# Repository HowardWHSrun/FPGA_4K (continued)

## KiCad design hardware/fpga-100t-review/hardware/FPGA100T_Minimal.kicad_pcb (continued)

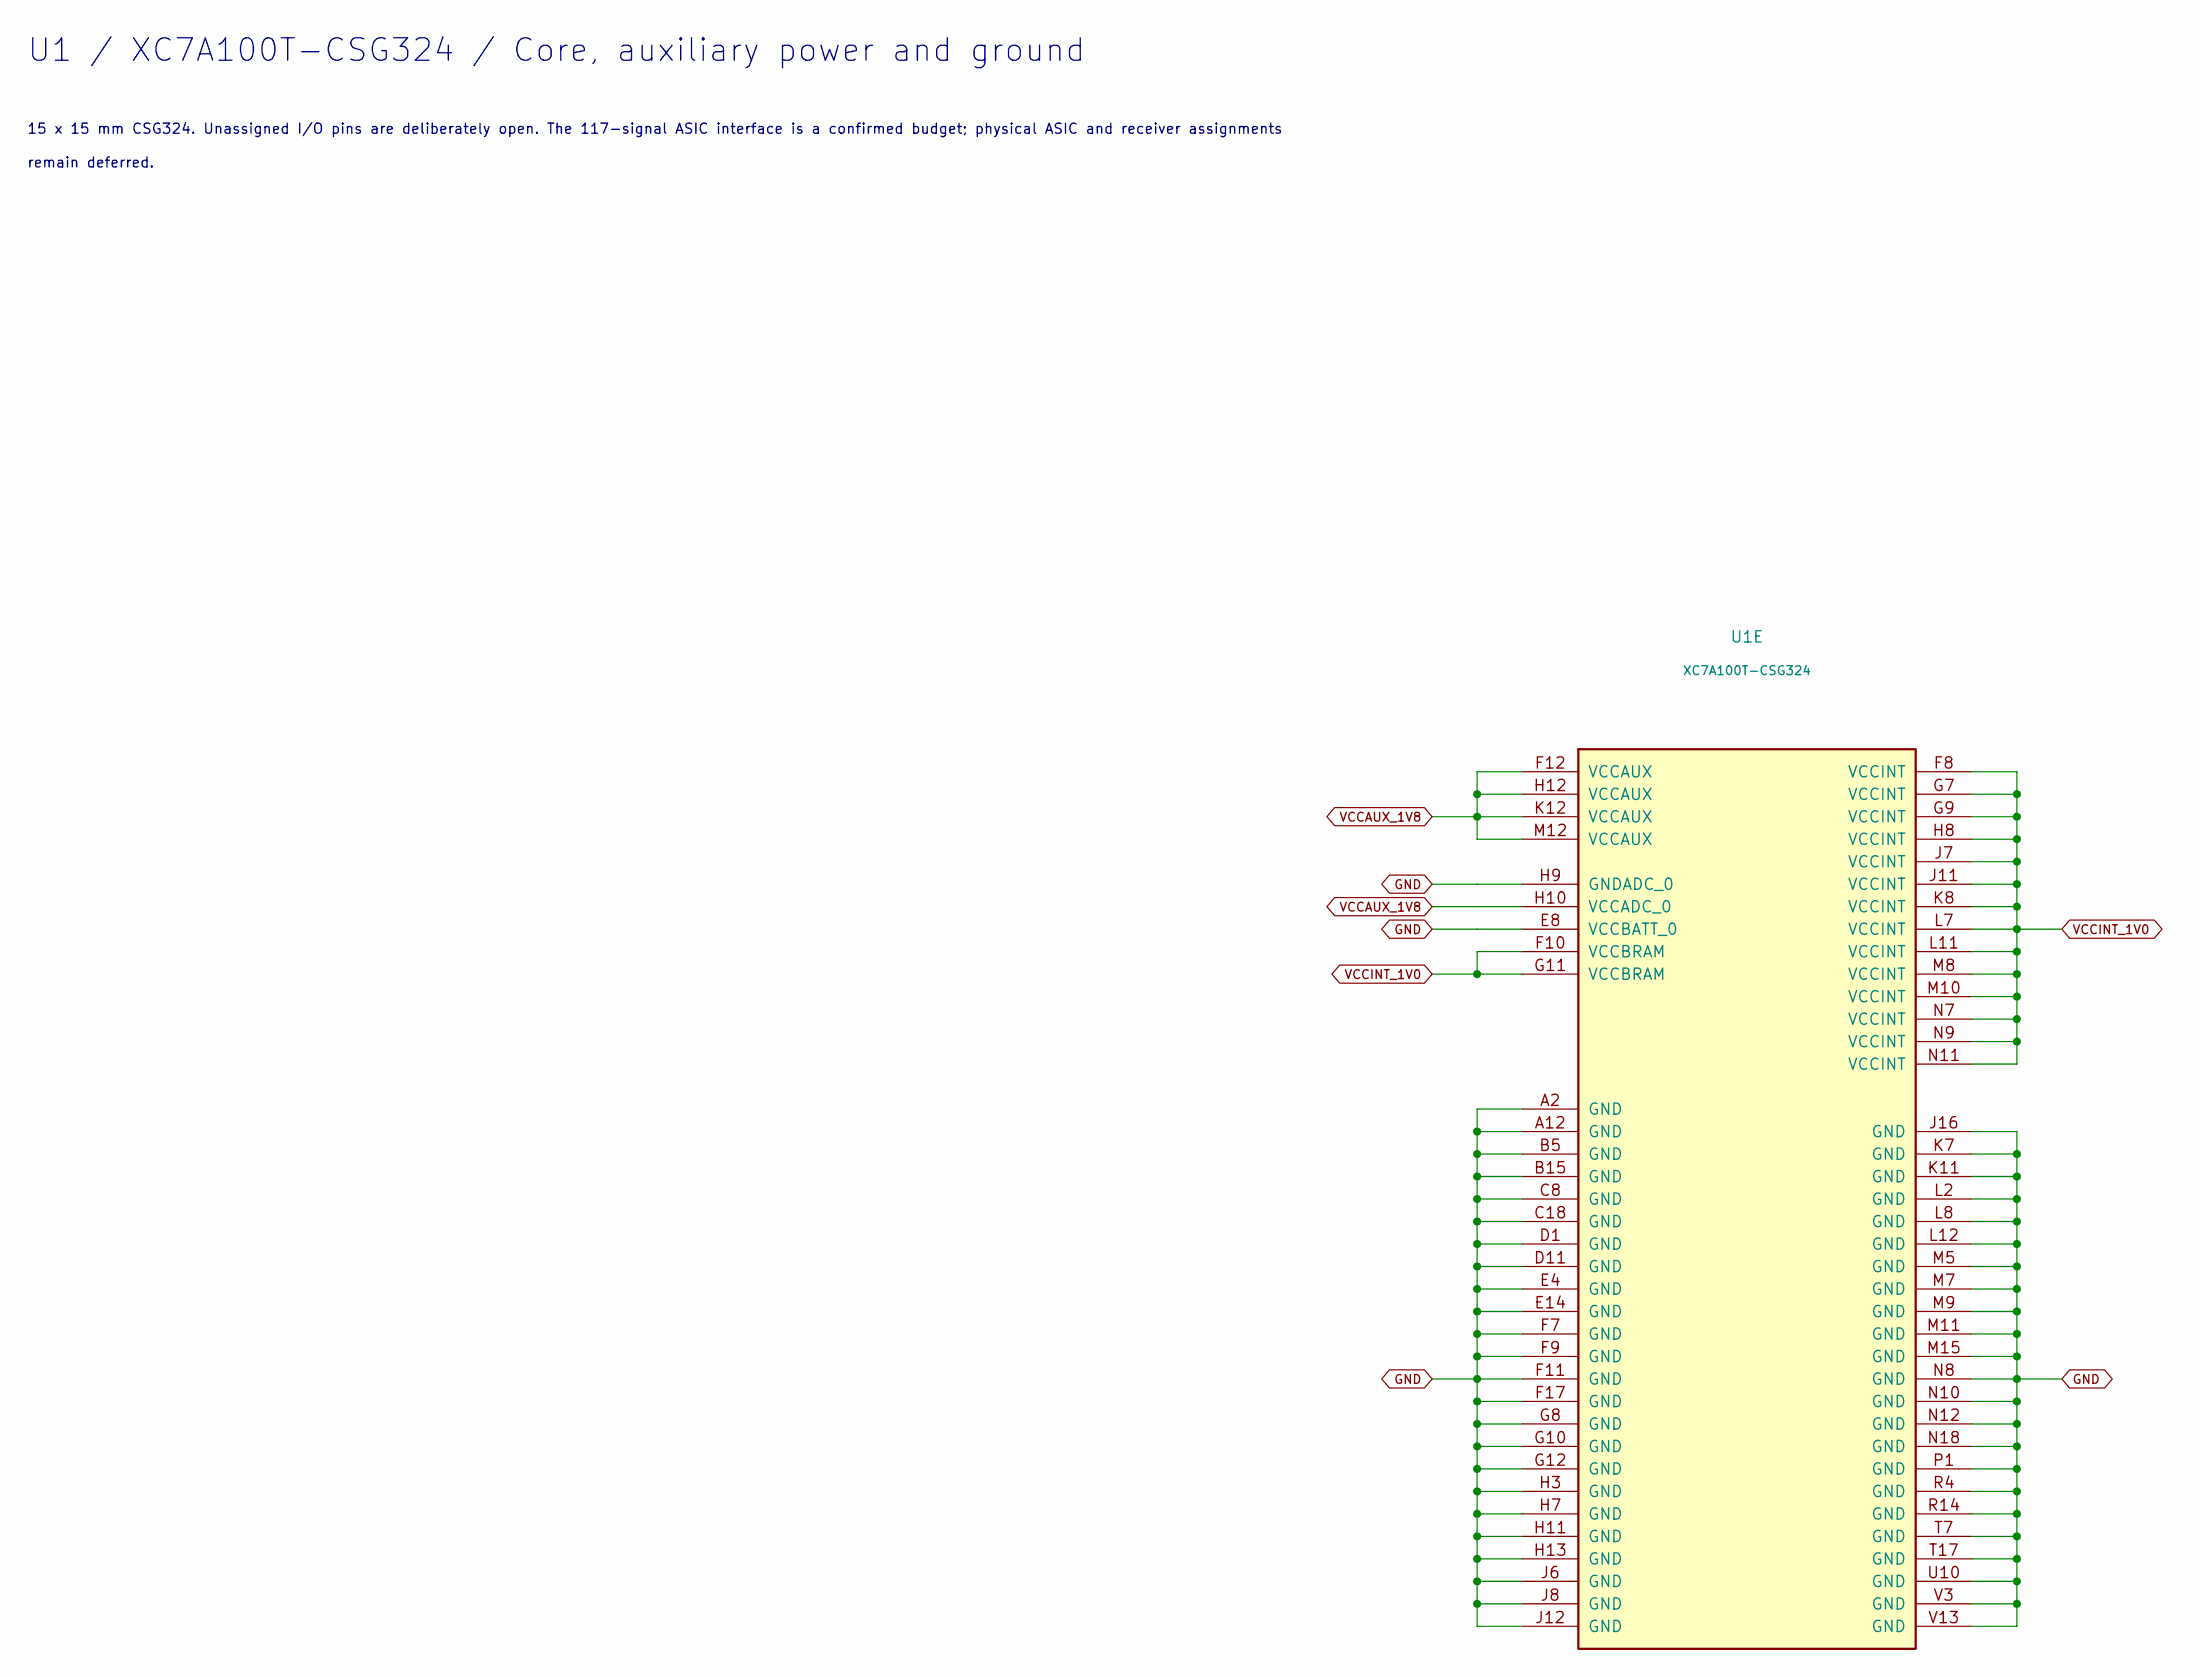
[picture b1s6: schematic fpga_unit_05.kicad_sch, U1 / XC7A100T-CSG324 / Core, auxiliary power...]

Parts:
U1: XC7A100T-CSG324; Xilinx_CSG324; MPN XC7A100T — speed and temperature grade 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

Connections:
GND: U1.A2 (GND), U1.A12 (GND), U1.B5 (GND), U1.B15 (GND), U1.C8 (GND), U1.C18 (GND), U1.D1 (GND), U1.D11 (GND), U1.E4 (GND), U1.E8 (VCCBATT_0), U1.E14 (GND), U1.F7 (GND), U1.F9 (GND), U1.F11 (GND), U1.F17 (GND), U1.G8 (GND), U1.G10 (GND), U1.G12 (GND), U1.H3 (GND), U1.H7 (GND), U1.H9 (GNDADC_0), U1.H11 (GND), U1.H13 (GND), U1.J6 (GND), U1.J8 (GND), U1.J12 (GND), U1.J16 (GND), U1.K7 (GND), U1.K11 (GND), U1.L2 (GND), U1.L8 (GND), U1.L12 (GND), U1.M5 (GND), U1.M7 (GND), U1.M9 (GND), U1.M11 (GND), U1.M15 (GND), U1.N8 (GND), U1.N10 (GND), U1.N12 (GND), U1.N18 (GND), U1.P1 (GND), U1.R4 (GND), U1.R14 (GND), U1.T7 (GND), U1.T17 (GND), U1.U10 (GND), U1.V3 (GND), U1.V13 (GND); also elsewhere on the board
VCCAUX_1V8: U1.F12 (VCCAUX), U1.H10 (VCCADC_0), U1.H12 (VCCAUX), U1.K12 (VCCAUX), U1.M12 (VCCAUX); also elsewhere on the board
VCCINT_1V0: U1.F8 (VCCINT), U1.F10 (VCCBRAM), U1.G7 (VCCINT), U1.G9 (VCCINT), U1.G11 (VCCBRAM), U1.H8 (VCCINT), U1.J7 (VCCINT), U1.J11 (VCCINT), U1.K8 (VCCINT), U1.L7 (VCCINT), U1.L11 (VCCINT), U1.M8 (VCCINT), U1.M10 (VCCINT), U1.N7 (VCCINT), U1.N9 (VCCINT), U1.N11 (VCCINT); also elsewhere on the board

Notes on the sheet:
U1 / XC7A100T-CSG324 / Core, auxiliary power and ground
15 x 15 mm CSG324. Unassigned I/O pins are deliberately open. The 117-signal ASIC interface is a confirmed budget; physical ASIC and receiver assignments
remain deferred.

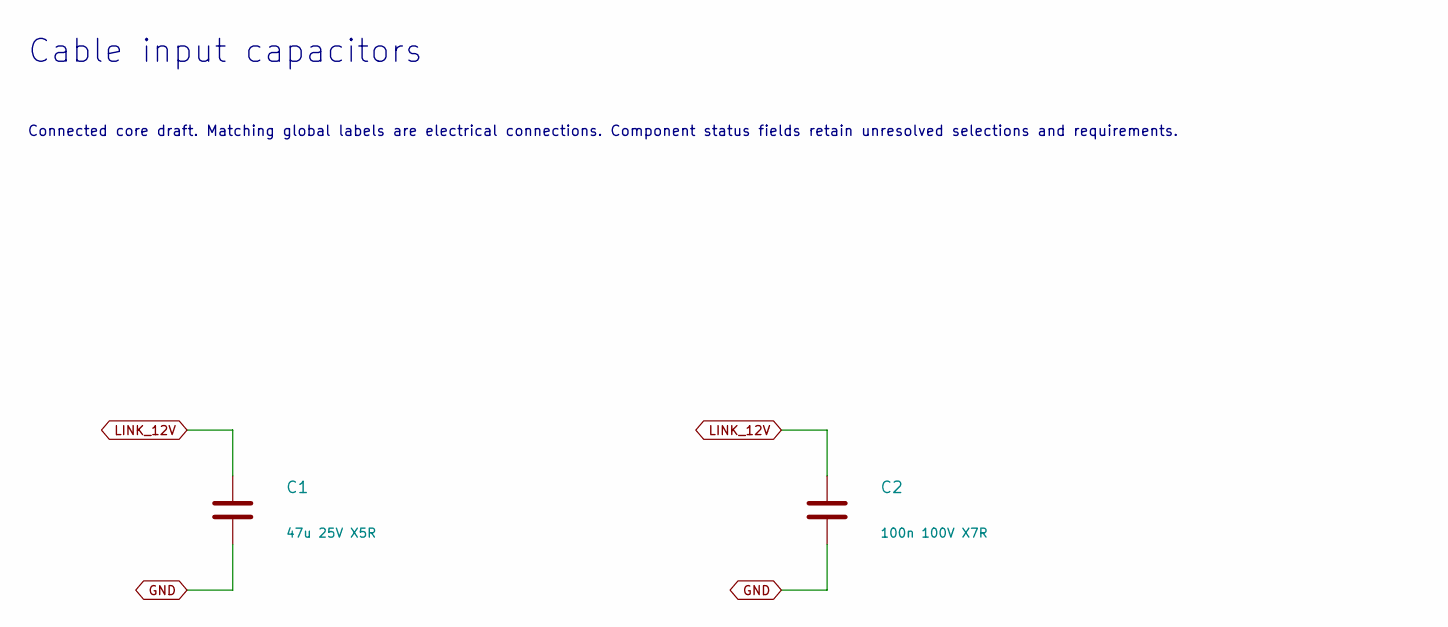
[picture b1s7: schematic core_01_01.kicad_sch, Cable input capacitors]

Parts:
C1: 47u 25V X5R; Capacitor_SMD__C_1210_3225Metric; MPN MSAST32MAB5476MPNDT1
C2: 100n 100V X7R; Capacitor_SMD__C_0603_1608Metric; MPN GRM188R72A104KA35D

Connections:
GND: C1.2, C2.2; also elsewhere on the board
LINK_12V: C1.1, C2.1; also elsewhere on the board

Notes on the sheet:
Cable input capacitors
Connected core draft. Matching global labels are electrical connections. Component status fields retain unresolved selections and requirements.

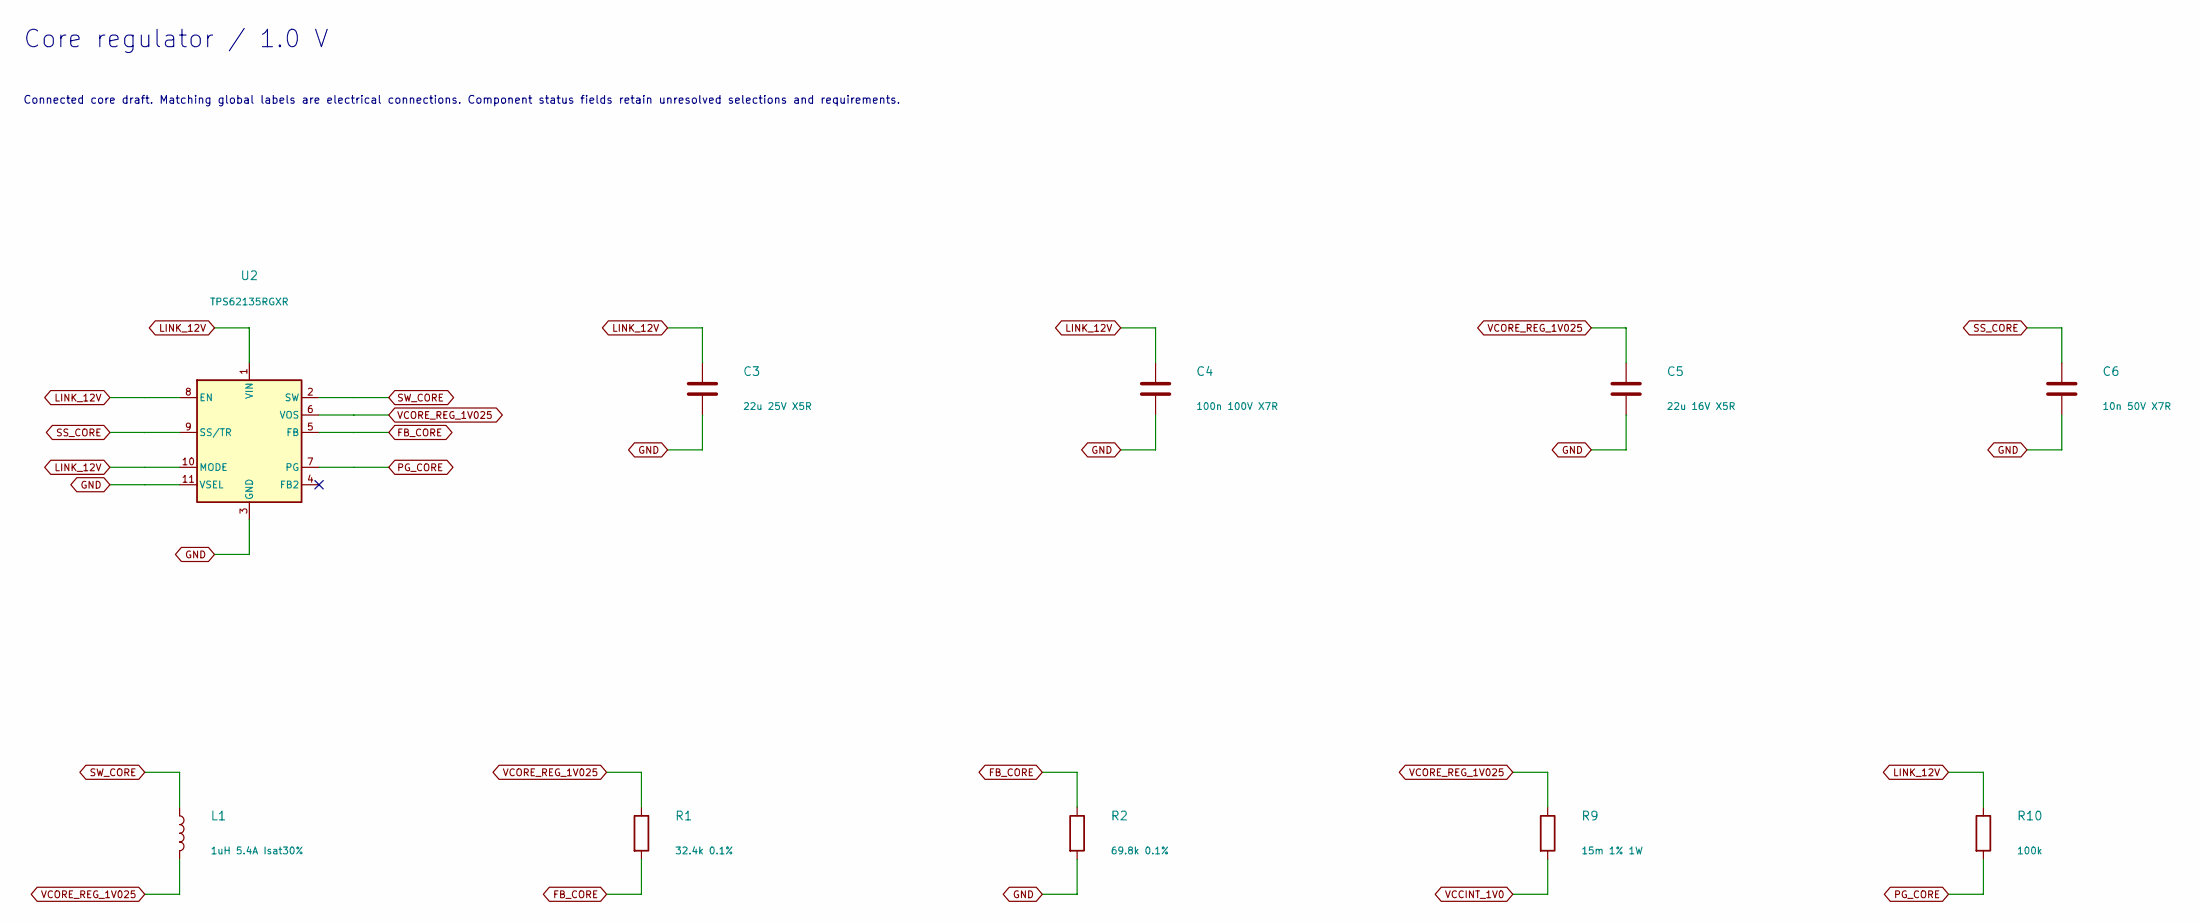
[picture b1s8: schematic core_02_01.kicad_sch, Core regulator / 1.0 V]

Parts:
C3: 22u 25V X5R; Capacitor_SMD__C_1206_3216Metric; MPN MSAST31LBB5226MTNA01
C4: 100n 100V X7R; Capacitor_SMD__C_0603_1608Metric; MPN GRM188R72A104KA35D
C5: 22u 16V X5R; Capacitor_SMD__C_0805_2012Metric; MPN EMK212BBJ226MG-T
C6: 10n 50V X7R; Capacitor_SMD__C_0603_1608Metric; MPN TBD - manufacturer/order code not selec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
L1: 1uH 5.4A Isat30%; PowerDraft__L_Coilcraft_XFL4020; MPN XFL4020-102MEC
R1: 32.4k 0.1%; Resistor_SMD__R_0603_1608Metric; MPN TBD - manufacturer/order code not selec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
R2: 69.8k 0.1%; Resistor_SMD__R_0603_1608Metric; MPN TBD - manufacturer/order code not selec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
R9: 15m 1% 1W; Resistor_SMD__R_1206_3216Metric; MPN WSLP1206R0150FEA
R10: 100k; Resistor_SMD__R_0603_1608Metric; MPN TBD - manufacturer/order code not selec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
U2: TPS62135RGXR; PowerDraft__Texas_VQFN_RGX0011A_2x3mm; MPN TPS62135RGXR

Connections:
FB_CORE: R1.2, R2.1, U2.5 (FB)
GND: C3.2, C4.2, C5.2, C6.2, R2.2, U2.3 (GND), U2.11 (VSEL); also elsewhere on the board
LINK_12V: C3.1, C4.1, R10.1, U2.1 (VIN), U2.8 (EN), U2.10 (MODE); also elsewhere on the board
PG_CORE: R10.2, U2.7 (PG); also elsewhere on the board
SS_CORE: C6.1, U2.9 (SS/TR)
SW_CORE: L1.1, U2.2 (SW)
VCCINT_1V0: R9.2; also elsewhere on the board
VCORE_REG_1V025: C5.1, L1.2, R1.1, R9.1, U2.6 (VOS)

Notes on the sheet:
Core regulator / 1.0 V
Connected core draft. Matching global labels are electrical connections. Component status fields retain unresolved selections and requirements.

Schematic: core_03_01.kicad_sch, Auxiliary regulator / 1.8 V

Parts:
C7: 22u 25V X5R; Capacitor_SMD__C_1206_3216Metric; MPN MSAST31LBB5226MTNA01
C8: 100n 100V X7R; Capacitor_SMD__C_0603_1608Metric; MPN GRM188R72A104KA35D
C9: 22u 16V X5R; Capacitor_SMD__C_0805_2012Metric; MPN EMK212BBJ226MG-T
C10: 10n 50V X7R; Capacitor_SMD__C_0603_1608Metric; MPN TBD - manufacturer/order code not selec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
L2: 1uH 5.4A Isat30%; PowerDraft__L_Coilcraft_XFL4020; MPN XFL4020-102MEC
R3: 110k 0.1%; Resistor_SMD__R_0603_1608Metric; MPN TBD - manufacturer/order code not selec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
R4: 69.8k 0.1%; Resistor_SMD__R_0603_1608Metric; MPN TBD - manufacturer/order code not selec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
R11: 100k; Resistor_SMD__R_0603_1608Metric; MPN TBD - manufacturer/order code not selec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
U3: TPS62135RGXR; PowerDraft__Texas_VQFN_RGX0011A_2x3mm; MPN TPS62135RGXR

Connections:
FB_AUX: R3.2, R4.1, U3.5 (FB)
GND: C7.2, C8.2, C9.2, C10.2, R4.2, U3.3 (GND), U3.11 (VSEL); also elsewhere on the board
LINK_12V: C7.1, C8.1, R11.1, U3.1 (VIN), U3.10 (MODE); also elsewhere on the board
PG_AUX: R11.2, U3.7 (PG); also elsewhere on the board
PG_CORE: U3.8 (EN); also elsewhere on the board
SS_AUX: C10.1, U3.9 (SS/TR)
SW_AUX: L2.1, U3.2 (SW)
VCCAUX_1V8: C9.1, L2.2, R3.1, U3.6 (VOS); also elsewhere on the board

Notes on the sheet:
Auxiliary regulator / 1.8 V
Connected core draft. Matching global labels are electrical connections. Component status fields retain unresolved selections and requirements.

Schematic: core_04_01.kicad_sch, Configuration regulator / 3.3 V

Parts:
C11: 22u 25V X5R; Capacitor_SMD__C_1206_3216Metric; MPN MSAST31LBB5226MTNA01
C12: 100n 100V X7R; Capacitor_SMD__C_0603_1608Metric; MPN GRM188R72A104KA35D
C13: 22u 16V X5R; Capacitor_SMD__C_0805_2012Metric; MPN EMK212BBJ226MG-T
C14: 10n 50V X7R; Capacitor_SMD__C_0603_1608Metric; MPN TBD - manufacturer/order code not selec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
L3: 1uH 5.4A Isat30%; PowerDraft__L_Coilcraft_XFL4020; MPN XFL4020-102MEC
R5: 261k 0.1%; Resistor_SMD__R_0603_1608Metric; MPN TBD - manufacturer/order code not selec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
R6: 69.8k 0.1%; Resistor_SMD__R_0603_1608Metric; MPN TBD - manufacturer/order code not selec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
R12: 100k; Resistor_SMD__R_0603_1608Metric; MPN TBD - manufacturer/order code not selec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
U4: TPS62135RGXR; PowerDraft__Texas_VQFN_RGX0011A_2x3mm; MPN TPS62135RGXR

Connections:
FB_CFG: R5.2, R6.1, U4.5 (FB)
GND: C11.2, C12.2, C13.2, C14.2, R6.2, U4.3 (GND), U4.11 (VSEL); also elsewhere on the board
LINK_12V: C11.1, C12.1, U4.1 (VIN), U4.10 (MODE); also elsewhere on the board
PGOOD_IO: R12.2, U4.7 (PG); also elsewhere on the board
PG_AUX: U4.8 (EN); also elsewhere on the board
SS_CFG: C14.1, U4.9 (SS/TR)
SW_CFG: L3.1, U4.2 (SW)
VCC_CFG_3V3: C13.1, L3.2, R5.1, R12.1, U4.6 (VOS); also elsewhere on the board

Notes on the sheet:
Configuration regulator / 3.3 V
Connected core draft. Matching global labels are electrical connections. Component status fields retain unresolved selections and requirements.

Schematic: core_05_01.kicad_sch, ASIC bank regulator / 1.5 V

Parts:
C15: 22u 25V X5R; Capacitor_SMD__C_1206_3216Metric; MPN MSAST31LBB5226MTNA01
C16: 100n 100V X7R; Capacitor_SMD__C_0603_1608Metric; MPN GRM188R72A104KA35D
C17: 22u 16V X5R; Capacitor_SMD__C_0805_2012Metric; MPN EMK212BBJ226MG-T
C18: 10n 50V X7R; Capacitor_SMD__C_0603_1608Metric; MPN TBD - manufacturer/order code not selec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
L4: 1uH 5.4A Isat30%; PowerDraft__L_Coilcraft_XFL4020; MPN XFL4020-102MEC
R7: 80.6k 0.1%; Resistor_SMD__R_0603_1608Metric; MPN TBD - manufacturer/order code not selec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
R8: 69.8k 0.1%; Resistor_SMD__R_0603_1608Metric; MPN TBD - manufacturer/order code not selec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
U5: TPS62135RGXR; PowerDraft__Texas_VQFN_RGX0011A_2x3mm; MPN TPS62135RGXR

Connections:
FB_ASIC: R7.2, R8.1, U5.5 (FB)
GND: C15.2, C16.2, C17.2, C18.2, R8.2, U5.3 (GND), U5.11 (VSEL); also elsewhere on the board
LINK_12V: C15.1, C16.1, U5.1 (VIN), U5.10 (MODE); also elsewhere on the board
PGOOD_IO: U5.7 (PG); also elsewhere on the board
PG_AUX: U5.8 (EN); also elsewhere on the board
SS_ASIC: C18.1, U5.9 (SS/TR)
SW_ASIC: L4.1, U5.2 (SW)
VCC_ASIC_1V5: C17.1, L4.2, R7.1, U5.6 (VOS); also elsewhere on the board

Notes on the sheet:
ASIC bank regulator / 1.5 V
Connected core draft. Matching global labels are electrical connections. Component status fields retain unresolved selections and requirements.

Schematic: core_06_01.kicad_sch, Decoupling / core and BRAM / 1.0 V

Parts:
C20: 330u 2.5V polymer ESR25m; Capacitor_Tantalum_SMD__CP_EIA-7343-20_Kemet-V; MPN T520V337M2R5ATE025
C21: 100u 6.3V X5R; Capacitor_SMD__C_1210_3225Metric; MPN GRM32ER60J107ME20L
C22, C23, C24, C25, C26, C27: 4.7u 10V X7R; Capacitor_SMD__C_0805_2012Metric; MPN GRM21BR71A475KA73L
C28, C29, C30, C31, C32, C33, C34, C35, C36, C37: 470n 6.3V X7R; Capacitor_SMD__C_0603_1608Metric; MPN GRM188R70J474KA01D

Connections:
GND: C20.2, C21.2, C22.2, C23.2, C24.2, C25.2, C26.2, C27.2, C28.2, C29.2, C30.2, C31.2, C32.2, C33.2, C34.2, C35.2, C36.2, C37.2; also elsewhere on the board
VCCINT_1V0: C20.1, C21.1, C22.1, C23.1, C24.1, C25.1, C26.1, C27.1, C28.1, C29.1, C30.1, C31.1, C32.1, C33.1, C34.1, C35.1, C36.1, C37.1; also elsewhere on the board

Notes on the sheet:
Decoupling / core and BRAM / 1.0 V
Connected core draft. Matching global labels are electrical connections. Component status fields retain unresolved selections and requirements.

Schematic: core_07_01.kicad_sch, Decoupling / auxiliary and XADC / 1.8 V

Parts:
C40: 47u 6.3V X7R; Capacitor_SMD__C_1210_3225Metric; MPN GRM32ER70J476ME20L
C41, C42: 4.7u 10V X7R; Capacitor_SMD__C_0805_2012Metric; MPN GRM21BR71A475KA73L
C43, C44, C45, C46: 470n 6.3V X7R; Capacitor_SMD__C_0603_1608Metric; MPN GRM188R70J474KA01D
C90: 100n 16V X7R; Capacitor_SMD__C_0603_1608Metric; MPN TBD - manufacturer/order code not selec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
C91: 1u 10V X7R; Capacitor_SMD__C_0603_1608Metric; MPN TBD - manufacturer/order code not selec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

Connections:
GND: C40.2, C41.2, C42.2, C43.2, C44.2, C45.2, C46.2, C90.2, C91.2; also elsewhere on the board
VCCAUX_1V8: C40.1, C41.1, C42.1, C43.1, C44.1, C45.1, C46.1, C90.1, C91.1; also elsewhere on the board

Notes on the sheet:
Decoupling / auxiliary and XADC / 1.8 V
Connected core draft. Matching global labels are electrical connections. Component status fields retain unresolved selections and requirements.

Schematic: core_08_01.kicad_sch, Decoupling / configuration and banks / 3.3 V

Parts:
C50, C63: 47u 6.3V X7R; Capacitor_SMD__C_1210_3225Metric; MPN GRM32ER70J476ME20L
C51, C52, C57, C58: 4.7u 10V X7R; Capacitor_SMD__C_0805_2012Metric; MPN GRM21BR71A475KA73L
C53, C54, C55, C56, C59, C60, C61, C62: 470n 6.3V X7R; Capacitor_SMD__C_0603_1608Metric; MPN GRM188R70J474KA01D

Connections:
GND: C50.2, C51.2, C52.2, C53.2, C54.2, C55.2, C56.2, C57.2, C58.2, C59.2, C60.2, C61.2, C62.2, C63.2; also elsewhere on the board
VCC_CFG_3V3: C50.1, C51.1, C52.1, C53.1, C54.1, C55.1, C56.1, C57.1, C58.1, C59.1, C60.1, C61.1, C62.1, C63.1; also elsewhere on the board

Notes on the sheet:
Decoupling / configuration and banks / 3.3 V
Connected core draft. Matching global labels are electrical connections. Component status fields retain unresolved selections and requirements.

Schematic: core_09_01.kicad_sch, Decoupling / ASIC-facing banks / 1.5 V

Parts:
C64, C65, C70, C71, C76, C77: 4.7u 10V X7R; Capacitor_SMD__C_0805_2012Metric; MPN GRM21BR71A475KA73L
C66, C67, C68, C69, C72, C73, C74, C75, C78, C79, C80, C81: 470n 6.3V X7R; Capacitor_SMD__C_0603_1608Metric; MPN GRM188R70J474KA01D
C82: 47u 6.3V X7R; Capacitor_SMD__C_1210_3225Metric; MPN GRM32ER70J476ME20L

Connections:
GND: C64.2, C65.2, C66.2, C67.2, C68.2, C69.2, C70.2, C71.2, C72.2, C73.2, C74.2, C75.2, C76.2, C77.2, C78.2, C79.2, C80.2, C81.2, C82.2; also elsewhere on the board
VCC_ASIC_1V5: C64.1, C65.1, C66.1, C67.1, C68.1, C69.1, C70.1, C71.1, C72.1, C73.1, C74.1, C75.1, C76.1, C77.1, C78.1, C79.1, C80.1, C81.1, C82.1; also elsewhere on the board

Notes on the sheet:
Decoupling / ASIC-facing banks / 1.5 V
Connected core draft. Matching global labels are electrical connections. Component status fields retain unresolved selections and requirements.

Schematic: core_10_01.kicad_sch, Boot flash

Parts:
C100: 100n; Capacitor_SMD__C_0402_1005Metric; MPN TBD_0402_X7R_16V_100n
C101: 1u; Capacitor_SMD__C_0402_1005Metric; MPN TBD_0402_X7R_16V_1u
R100: 2.4k; Resistor_SMD__R_0402_1005Metric; MPN TBD_0402_1pct_2.4k
R101, R102: 4.7k; Resistor_SMD__R_0402_1005Metric; MPN TBD_0402_1pct_4.7k
R103, R105: 33; Resistor_SMD__R_0402_1005Metric; MPN TBD_0402_1pct_33
R104, R106, R107: 0; Resistor_SMD__R_0402_1005Metric; MPN TBD_0402_1pct_0
U6: MX25L12833FM2I-10G; Package_SO__SOIC-8_5_3x5_3mm_P1_27mm; MPN MX25L12833FM2I-10G

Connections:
FLASH_CS_B: R100.2, U6.1 (~CS); also elsewhere on the board
FLASH_DQ0: R104.2, U6.5 (SI/SIO0)
FLASH_DQ1: R105.2, U6.2 (SO/SIO1)
FLASH_DQ2: R101.2, R106.2, U6.3 (~WP/SIO2)
FLASH_DQ3: R102.2, R107.2, U6.7 (~RESET/SIO3)
FLASH_SCLK: R103.2, U6.6 (SCLK)
FPGA_CCLK: R103.1; also elsewhere on the board
FPGA_CFG_DQ0: R104.1; also elsewhere on the board
FPGA_CFG_DQ1: R105.1; also elsewhere on the board
FPGA_CFG_DQ2: R106.1; also elsewhere on the board
FPGA_CFG_DQ3: R107.1; also elsewhere on the board
GND: C100.2, C101.2, U6.4 (GND); also elsewhere on the board
VCC_CFG_3V3: C100.1, C101.1, R100.1, R101.1, R102.1, U6.8 (VCC); also elsewhere on the board

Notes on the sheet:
Boot flash
Connected core draft. Matching global labels are electrical connections. Component status fields retain unresolved selections and requirements.

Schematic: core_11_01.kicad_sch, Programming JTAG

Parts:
R108, R109, R110: 4.7k; Resistor_SMD__R_0402_1005Metric; MPN TBD_0402_1pct_4.7k
R111, R112, R113, R114: 1k; Resistor_SMD__R_0402_1005Metric; MPN TBD_0402_1pct_1k
R115, R116, R117: 10k; Resistor_SMD__R_0402_1005Metric; MPN TBD_0402_1pct_10k
R118: 33; Resistor_SMD__R_0402_1005Metric; MPN TBD_0402_1pct_33

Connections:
CFG_M0: R111.2; also elsewhere on the board
CFG_M1: R112.1; also elsewhere on the board
CFG_M2: R113.1; also elsewhere on the board
CFG_PUDC_B: R114.2; also elsewhere on the board
FPGA_DONE: R110.2; also elsewhere on the board
FPGA_INIT_B: R109.2; also elsewhere on the board
FPGA_PROGRAM_B: R108.2; also elsewhere on the board
FPGA_TDO: R118.1; also elsewhere on the board
GND: R112.2, R113.2; also elsewhere on the board
JTAG_TCK: R117.2; also elsewhere on the board
JTAG_TDI: R116.2; also elsewhere on the board
JTAG_TDO: R118.2; also elsewhere on the board
JTAG_TMS: R115.2; also elsewhere on the board
VCC_CFG_3V3: R108.1, R109.1, R110.1, R111.1, R114.1, R115.1, R116.1, R117.1; also elsewhere on the board

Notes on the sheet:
Programming JTAG
Connected core draft. Matching global labels are electrical connections. Component status fields retain unresolved selections and requirements.

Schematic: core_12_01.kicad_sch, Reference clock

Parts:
C102: 10n; Capacitor_SMD__C_0402_1005Metric; MPN TBD_0402_X7R_16V_10n
C103: 100n; Capacitor_SMD__C_0402_1005Metric; MPN TBD_0402_X7R_16V_100n
R119: 33; Resistor_SMD__R_0402_1005Metric; MPN TBD_0402_1pct_33
Y1: ASE-32.000MHZ-L-C-T; Oscillator__Oscillator_SMD_Abracon_ASE-4Pin_3_2x2_5mm; MPN ASE-32.000MHZ-L-C-T

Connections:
CLK_32MHZ: R119.2; also elsewhere on the board
GND: C102.2, C103.2, Y1.2 (GND); also elsewhere on the board
OSC_32M_RAW: R119.1, Y1.3 (OUT)
VCC_CFG_3V3: C102.1, C103.1, Y1.1 (EN), Y1.4 (Vdd); also elsewhere on the board

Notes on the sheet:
Reference clock
Connected core draft. Matching global labels are electrical connections. Component status fields retain unresolved selections and requirements.

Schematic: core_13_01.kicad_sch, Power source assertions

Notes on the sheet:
Power source assertions
Connected core draft. Matching global labels are electrical connections. Component status fields retain unresolved selections and requirements.

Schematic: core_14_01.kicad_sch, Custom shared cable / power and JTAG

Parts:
J4: CUSTOM POWER + JTAG / DATA TBD; LinkPort__MicroHDMI_46765_1xxx; MPN Molex46765 family; exact order code pen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

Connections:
GND: J4.4 (GND), J4.7 (GND), J4.10 (GND), J4.13 (GND), J4.16 (GND), J4.SH (GND); also elsewhere on the board
JTAG_TCK: J4.17 (JTAG_TCK); also elsewhere on the board
JTAG_TDI: J4.15 (JTAG_TDI); also elsewhere on the board
JTAG_TDO: J4.18 (JTAG_TDO); also elsewhere on the board
JTAG_TMS: J4.2 (JTAG_TMS); also elsewhere on the board
LINK_12V: J4.19 (12V); also elsewhere on the board
VCC_CFG_3V3: J4.1 (VTREF); also elsewhere on the board

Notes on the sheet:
Custom shared cable / power and JTAG
Connected core draft. Matching global labels are electrical connections. Component status fields retain unresolved selections and requirements.
J4 / one custom cable connector
Contact
Net
Function
LINK_12V
Power input, proposed nominal 12 V
GND
DC return
VCC_CFG_3V3
Target voltage reference for programmer
JTAG_TMS
Programmer to FPGA E12
JTAG_TDI
Programmer to FPGA E11
JTAG_TCK
Programmer to FPGA E10
JTAG_TDO
FPGA E13 via R118 to programmer
4, 7, 10, 13, SH
Pair shields and shell
Pins 3/5, 6/8, 9/11 and 12/14: reserved data pairs, not yet assigned.
12 V is a design proposal, not a qualified cable-power specification.
Requires a protected source and verified cable/contact current ratings.
Do not connect this custom-powered port to ordinary HDMI equipment.
No separate JTAG header, boot-mode jumper or test points.

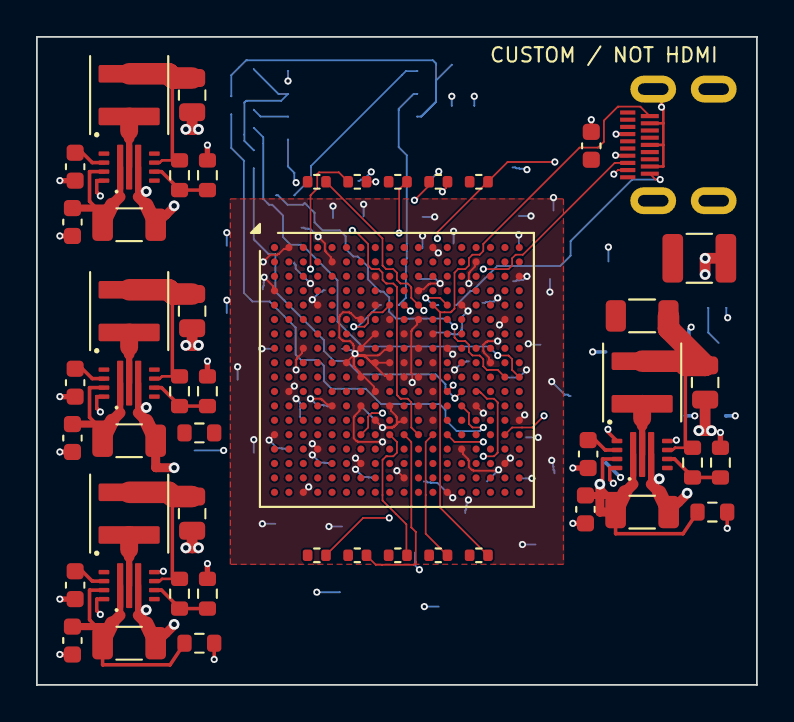
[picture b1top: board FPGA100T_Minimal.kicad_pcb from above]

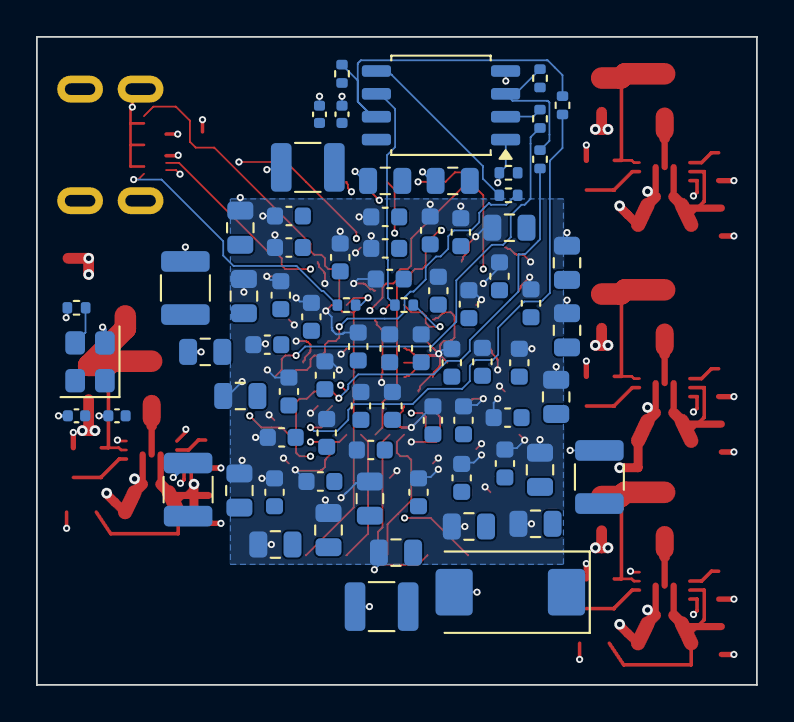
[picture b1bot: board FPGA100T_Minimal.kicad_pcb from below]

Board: 6 copper layers, 40.0 x 36.0 mm, 126 parts (76 on the bottom side), 47 nets.

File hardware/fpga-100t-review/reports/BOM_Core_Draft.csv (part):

Reference,Quantity,Value,MPN,Footprint,Group,Status,DNP
U1,1,XC7A100T-CSG324,XC7A100T — speed and temperature grade TBD,FPGA100T:Xilinx_CSG324,FPGA,Engineering draft; normal 1.0 V core grade assumed; 117 application signals reserved but unassigned,False
C1,1,47u 25V X5R,MSAST32MAB5476MPNDT1,CoreSupport:Capacitor_SMD__C_1210_3225Metric,power_input,"12V candidate: manufacturer confirms 47uF +/-20%, 25V X5R, 1210, -55 to +85C, preferred part; effective capacitance at 12V, aging, temperature, inrush and power-entry transient performance remain unqualified. Replaces incompatible 10V input capacitor.",False
C2,1,100n 100V X7R,GRM188R72A104KA35D,CoreSupport:Capacitor_SMD__C_0603_1608Metric,power_input,"12V candidate: manufacturer confirms 100nF +/-10%, 100V X7R, 0603, -55 to +125C and D packing suffix. Input bypass only; this voltage rating does not protect the 17V-rated converter input from cable transients.",False
U2,1,TPS62135RGXR,TPS62135RGXR,CoreSupport:PowerDraft__Texas_VQFN_RGX0011A_2x3mm,power_core,Engineering draft; verify ordered part and layout before fabrication,False
L1,1,1uH 5.4A Isat30%,XFL4020-102MEC,CoreSupport:PowerDraft__L_Coilcraft_XFL4020,power_core,Engineering draft; verify ordered part and layout before fabrication,False
R1,1,32.4k 0.1%,TBD - manufacturer/order code not selected,CoreSupport:Resistor_SMD__R_0603_1608Metric,power_core,Engineering draft; verify ordered part and layout before fabrication,False
R2,1,69.8k 0.1%,TBD - manufacturer/order code not selected,CoreSupport:Resistor_SMD__R_0603_1608Metric,power_core,Engineering draft; verify ordered part and layout before fabrication,False
C3,1,22u 25V X5R,MSAST31LBB5226MTNA01,CoreSupport:Capacitor_SMD__C_1206_3216Metric,power_core,"12 V delegated design: 22 uF 25 V X5R 1206 replacement. Manufacturer typical bias curve gives 6.62332 uF at 12.6 V; 0.8 tolerance and 0.85 temperature screening factors give 4.5038576 uF before aging. Local placement and routing implemented. Typical curves do not guarantee production minimum; cable/source, thermal and full power delivery remain unqualified.",False
C4,1,100n 100V X7R,GRM188R72A104KA35D,CoreSupport:Capacitor_SMD__C_0603_1608Metric,power_core,"12V candidate: manufacturer confirms 100nF +/-10%, 100V X7R, 0603, -55 to +125C and D packing suffix. Input bypass only; this voltage rating does not protect the 17V-rated converter input from cable transients.",False
C5,1,22u 16V X5R,EMK212BBJ226MG-T,CoreSupport:Capacitor_SMD__C_0805_2012Metric,power_core,"Engineering draft; verify ordered part and layout before fabrication Independent review: X5R, rated -55 to +85 C; manufacturer renamed alias MSASE21GBB5226MTNA01; effective capacitance and sourcing not qualified.",False
C6,1,10n 50V X7R,TBD - manufacturer/order code not selected,CoreSupport:Capacitor_SMD__C_0603_1608Metric,power_core,Engineering draft; verify ordered part and layout before fabrication,False
U3,1,TPS62135RGXR,TPS62135RGXR,CoreSupport:PowerDraft__Texas_VQFN_RGX0011A_2x3mm,power_aux,Engineering draft; verify ordered part and layout before fabrication,False
L2,1,1uH 5.4A Isat30%,XFL4020-102MEC,CoreSupport:PowerDraft__L_Coilcraft_XFL4020,power_aux,Engineering draft; verify ordered part and layout before fabrication,False
R3,1,110k 0.1%,TBD - manufacturer/order code not selected,CoreSupport:Resistor_SMD__R_0603_1608Metric,power_aux,Engineering draft; verify ordered part and layout before fabrication,False
R4,1,69.8k 0.1%,TBD - manufacturer/order code not selected,CoreSupport:Resistor_SMD__R_0603_1608Metric,power_aux,Engineering draft; verify ordered part and layout before fabrication,False
C7,1,22u 25V X5R,MSAST31LBB5226MTNA01,CoreSupport:Capacitor_SMD__C_1206_3216Metric,power_aux,"12 V delegated design: 22 uF 25 V X5R 1206 replacement. Manufacturer typical bias curve gives 6.62332 uF at 12.6 V; 0.8 tolerance and 0.85 temperature screening factors give 4.5038576 uF before aging. Local placement and routing implemented. Typical curves do not guarantee production minimum; cable/source, thermal and full power delivery remain unqualified.",False
C8,1,100n 100V X7R,GRM188R72A104KA35D,CoreSupport:Capacitor_SMD__C_0603_1608Metric,power_aux,"12V candidate: manufacturer confirms 100nF +/-10%, 100V X7R, 0603, -55 to +125C and D packing suffix. Input bypass only; this voltage rating does not protect the 17V-rated converter input from cable transients.",False
C9,1,22u 16V X5R,EMK212BBJ226MG-T,CoreSupport:Capacitor_SMD__C_0805_2012Metric,power_aux,"Engineering draft; verify ordered part and layout before fabrication Independent review: X5R, rated -55 to +85 C; manufacturer renamed alias MSASE21GBB5226MTNA01; effective capacitance and sourcing not qualified.",False
C10,1,10n 50V X7R,TBD - manufacturer/order code not selected,CoreSupport:Capacitor_SMD__C_0603_1608Metric,power_aux,Engineering draft; verify ordered part and layout before fabrication,False
U4,1,TPS62135RGXR,TPS62135RGXR,CoreSupport:PowerDraft__Texas_VQFN_RGX0011A_2x3mm,power_cfg,Engineering draft; verify ordered part and layout before fabrication,False
L3,1,1uH 5.4A Isat30%,XFL4020-102MEC,CoreSupport:PowerDraft__L_Coilcraft_XFL4020,power_cfg,Engineering draft; verify ordered part and layout before fabrication,False
R5,1,261k 0.1%,TBD - manufacturer/order code not selected,CoreSupport:Resistor_SMD__R_0603_1608Metric,power_cfg,Engineering draft; verify ordered part and layout before fabrication,False
R6,1,69.8k 0.1%,TBD - manufacturer/order code not selected,CoreSupport:Resistor_SMD__R_0603_1608Metric,power_cfg,Engineering draft; verify ordered part and layout before fabrication,False
C11,1,22u 25V X5R,MSAST31LBB5226MTNA01,CoreSupport:Capacitor_SMD__C_1206_3216Metric,power_cfg,"12 V delegated design: 22 uF 25 V X5R 1206 replacement. Manufacturer typical bias curve gives 6.62332 uF at 12.6 V; 0.8 tolerance and 0.85 temperature screening factors give 4.5038576 uF before aging. Local placement and routing implemented. Typical curves do not guarantee production minimum; cable/source, thermal and full power delivery remain unqualified.",False
C12,1,100n 100V X7R,GRM188R72A104KA35D,CoreSupport:Capacitor_SMD__C_0603_1608Metric,power_cfg,"12V candidate: manufacturer confirms 100nF +/-10%, 100V X7R, 0603, -55 to +125C and D packing suffix. Input bypass only; this voltage rating does not protect the 17V-rated converter input from cable transients.",False
C13,1,22u 16V X5R,EMK212BBJ226MG-T,CoreSupport:Capacitor_SMD__C_0805_2012Metric,power_cfg,"Engineering draft; verify ordered part and layout before fabrication Independent review: X5R, rated -55 to +85 C; manufacturer renamed alias MSASE21GBB5226MTNA01; effective capacitance and sourcing not qualified.",False
C14,1,10n 50V X7R,TBD - manufacturer/order code not selected,CoreSupport:Capacitor_SMD__C_0603_1608Metric,power_cfg,Engineering draft; verify ordered part and layout before fabrication,False
U5,1,TPS62135RGXR,TPS62135RGXR,CoreSupport:PowerDraft__Texas_VQFN_RGX0011A_2x3mm,power_asic,Engineering draft; verify ordered part and layout before fabrication,False
L4,1,1uH 5.4A Isat30%,XFL4020-102MEC,CoreSupport:PowerDraft__L_Coilcraft_XFL4020,power_asic,Engineering draft; verify ordered part and layout before fabrication,False
R7,1,80.6k 0.1%,TBD - manufacturer/order code not selected,CoreSupport:Resistor_SMD__R_0603_1608Metric,power_asic,Engineering draft; verify ordered part and layout before fabrication,False
R8,1,69.8k 0.1%,TBD - manufacturer/order code not selected,CoreSupport:Resistor_SMD__R_0603_1608Metric,power_asic,Engineering draft; verify ordered part and layout before fabrication,False
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
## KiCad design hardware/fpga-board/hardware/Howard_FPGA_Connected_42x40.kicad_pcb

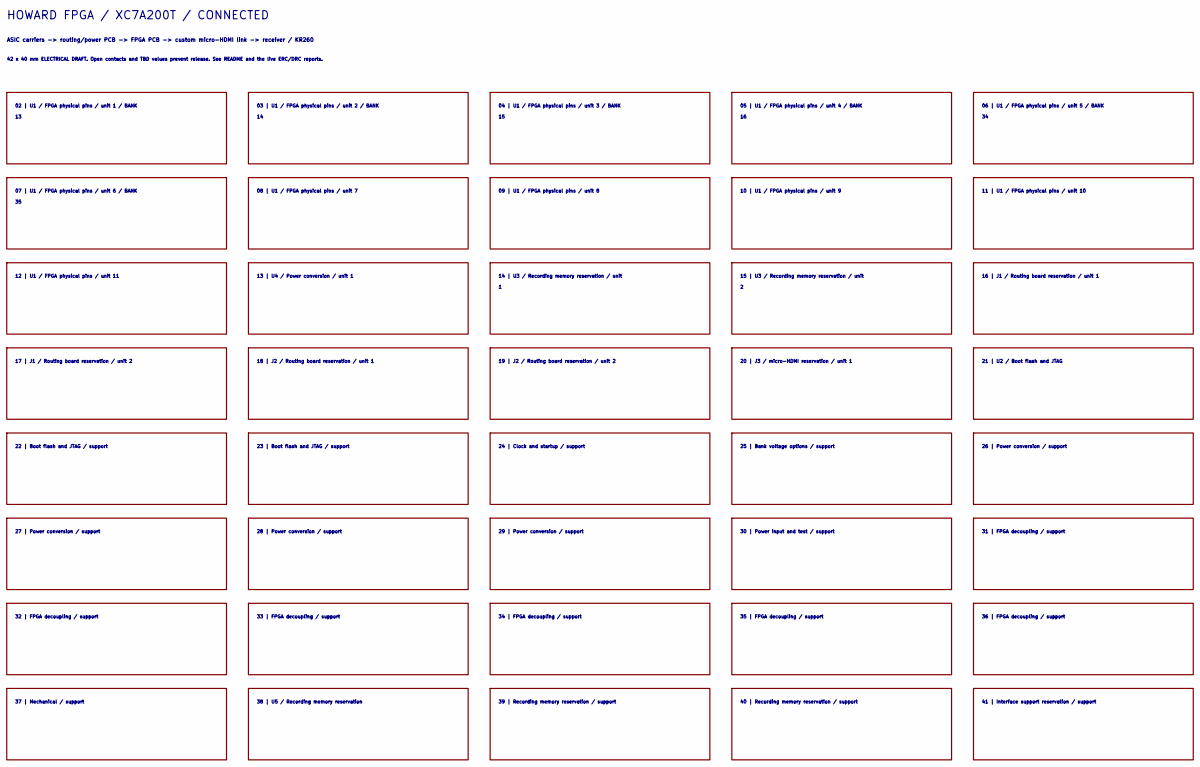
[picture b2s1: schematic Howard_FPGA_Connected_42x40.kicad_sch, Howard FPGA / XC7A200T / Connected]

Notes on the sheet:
22 | Boot flash and JTAG / support
17 | J1 / Routing board reservation / unit 2
30 | Power input and test / support
23 | Boot flash and JTAG / support
ASIC carriers -> routing/power PCB -> FPGA PCB -> custom micro-HDMI link -> receiver / KR260
03 | U1 / FPGA physical pins / unit 2 / BANK
05 | U1 / FPGA physical pins / unit 4 / BANK
18 | J2 / Routing board reservation / unit 1
31 | FPGA decoupling / support
06 | U1 / FPGA physical pins / unit 5 / BANK
35 | FPGA decoupling / support
32 | FPGA decoupling / support
34 | FPGA decoupling / support
04 | U1 / FPGA physical pins / unit 3 / BANK
21 | U2 / Boot flash and JTAG
11 | U1 / FPGA physical pins / unit 10
26 | Power conversion / support
09 | U1 / FPGA physical pins / unit 8
13 | U4 / Power conversion / unit 1
37 | Mechanical / support
33 | FPGA decoupling / support
24 | Clock and startup / support
HOWARD FPGA / XC7A200T / CONNECTED
28 | Power conversion / support
07 | U1 / FPGA physical pins / unit 6 / BANK
25 | Bank voltage options / support
16 | J1 / Routing board reservation / unit 1
36 | FPGA decoupling / support
42 x 40 mm ELECTRICAL DRAFT. Open contacts and TBD values prevent release. See README and the live ERC/DRC reports.
40 | Recording memory reservation / support
15 | U3 / Recording memory reservation / unit
08 | U1 / FPGA physical pins / unit 7
02 | U1 / FPGA physical pins / unit 1 / BANK
10 | U1 / FPGA physical pins / unit 9
41 | Interface support reservation / support
39 | Recording memory reservation / support
29 | Power conversion / support
27 | Power conversion / support
19 | J2 / Routing board reservation / unit 2
12 | U1 / FPGA physical pins / unit 11
